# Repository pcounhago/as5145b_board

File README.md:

# AS5145B magnetic encoder board

This board includes an [AMS AS5145B](https://ams.com/as5145b) magnetic encoder for robotics projects.

## Description

The [AMS AS5145B](https://ams.com/as5145b) is a 12 bit programmable magnetic rotary encoder that provides multiple outputs SSI, PWM and quadrature. This board configures the encoder to provide quadrature A/B and Index output signals. It generates 1024 pulses per revolution and is ideal for different robotics projects.

The board includes a JST connector with 1.5 mm pitch with the following signals:

Signal | Description
-------|-------------
V | Power supply (3.3 V)
G | Ground
A | First quadrature channel
B | Second quadrature channel

## BOM

Reference | Description | Quantity
------------ | ------------- | ------------- |
AS5145B-HSST | AS5145B 12-Bit Programmable Magnetic Rotary Encoder | 1
C1 | 0805 ceramic capacitor, 100nF | 1
J1 | JST B4B-ZR | 1

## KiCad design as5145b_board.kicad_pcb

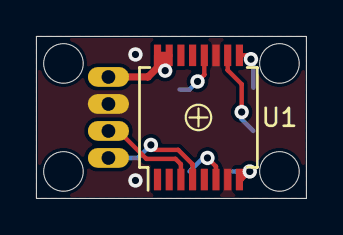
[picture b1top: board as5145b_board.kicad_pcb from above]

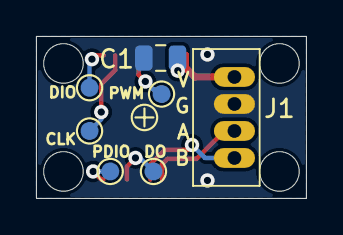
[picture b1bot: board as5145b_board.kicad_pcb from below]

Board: 2 copper layers, 15.0 x 9.0 mm, 3 parts (2 on the bottom side), 4 nets.

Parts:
C1: C; C_0805_2012Metric
J1: Conn_01x04_Male; B4B-ZR
U1: AS5145B-HSST; SSOP-16_5.3x6.2mm_P0.65mm

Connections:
+3V3: C1.1, J1.1, U1.15, U1.16
/DTest1_A: J1.3, U1.3
/DTest2_B: J1.4, U1.4
GND: C1.2, J1.2, U1.7, U1.11
